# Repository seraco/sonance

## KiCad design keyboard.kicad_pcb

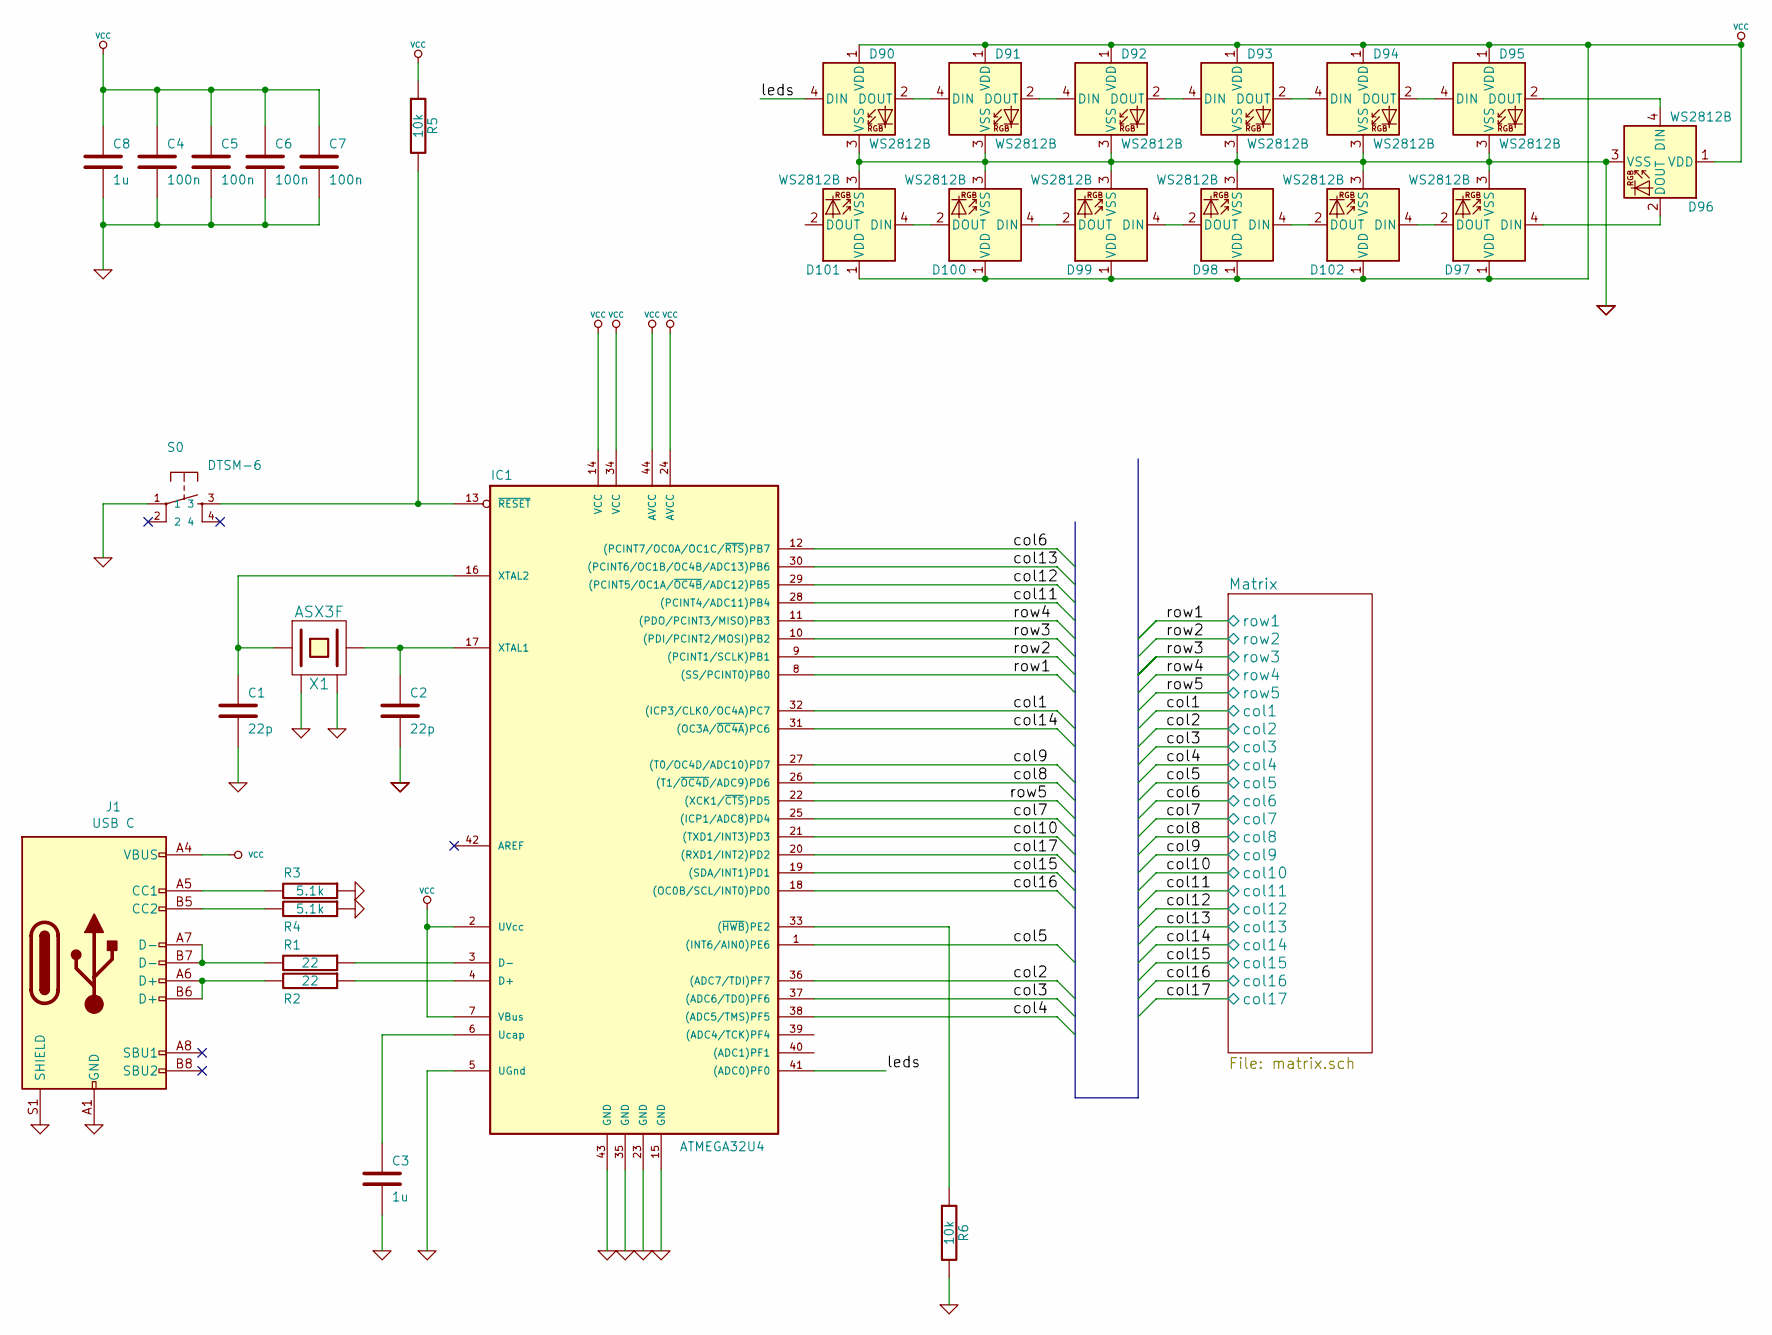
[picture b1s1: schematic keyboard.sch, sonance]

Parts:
C1, C2: 22p; 0805C; LCSC C1804
C3, C8: 1u; 0805C; LCSC C89190
C4, C5, C6, C7: 100n; 0805C; LCSC C1711
D90, D91, D92, D93, D94, D95, D96, D97, D98, D99, D100, D101, D102: WS2812B; LED_WS2812B_PLCC4_5.0x5.0mm_P3.2mm; LCSC C2761795
IC1: ATMEGA32U4; QFN-44-1EP_7x7mm_P0.5mm_EP5.2x5.2mm; LCSC C45874
J1: USB C; USB_C_Receptacle_Palconn_UTC16-G; LCSC C2835315
R1, R2: 22; 0805R; LCSC C17561
R3, R4: 5.1k; 0805R; LCSC C27834
R5, R6: 10k; 0805R; LCSC C17414
S0: DTSM-6; KSEM31GLFS; LCSC C221773
X1: ASX3F; 4-SMD; LCSC C258942

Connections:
/col1: IC1.32 ((ICP3/CLK0/OC4A)PC7); also elsewhere on the board
/col2: IC1.36 ((ADC7/TDI)PF7); also elsewhere on the board
/col3: IC1.37 ((ADC6/TDO)PF6); also elsewhere on the board
/col4: IC1.38 ((ADC5/TMS)PF5); also elsewhere on the board
/col5: IC1.1 ((INT6/AIN0)PE6); also elsewhere on the board
/col6: IC1.12 ((PCINT7/OC0A/OC1C/~RTS~)PB7); also elsewhere on the board
/col7: IC1.25 ((ICP1/ADC8)PD4); also elsewhere on the board
/col8: IC1.26 ((T1/~OC4D~/ADC9)PD6); also elsewhere on the board
/col9: IC1.27 ((T0/OC4D/ADC10)PD7); also elsewhere on the board
/col10: IC1.21 ((TXD1/INT3)PD3); also elsewhere on the board
/col11: IC1.28 ((PCINT4/ADC11)PB4); also elsewhere on the board
/col12: IC1.29 ((PCINT5/OC1A/~OC4B~/ADC12)PB5); also elsewhere on the board
/col13: IC1.30 ((PCINT6/OC1B/OC4B/ADC13)PB6); also elsewhere on the board
/col14: IC1.31 ((OC3A/~OC4A~)PC6); also elsewhere on the board
/col15: IC1.19 ((SDA/INT1)PD1); also elsewhere on the board
/col16: IC1.18 ((OC0B/SCL/INT0)PD0); also elsewhere on the board
/col17: IC1.20 ((RXD1/INT2)PD2); also elsewhere on the board
/leds: D90.4 (DIN), IC1.41 ((ADC0)PF0)
/row1: IC1.8 ((SS/PCINT0)PB0); also elsewhere on the board
/row2: IC1.9 ((PCINT1/SCLK)PB1); also elsewhere on the board
/row3: IC1.10 ((PDI/PCINT2/MOSI)PB2); also elsewhere on the board
/row4: IC1.11 ((PDO/PCINT3/MISO)PB3); also elsewhere on the board
/row5: IC1.22 ((XCK1/~CTS~)PD5); also elsewhere on the board
GND: C1.2, C2.2, C3.2, C4.2, C5.2, C6.2, C7.2, C8.2, D90.3 (VSS), D91.3 (VSS), D92.3 (VSS), D93.3 (VSS), D94.3 (VSS), D95.3 (VSS), D96.3 (VSS), D97.3 (VSS), D98.3 (VSS), D99.3 (VSS), D100.3 (VSS), D101.3 (VSS), D102.3 (VSS), IC1.5 (UGnd), IC1.15 (GND), IC1.23 (GND), IC1.35 (GND), IC1.43 (GND), J1.A1 (GND), J1.A12 (GND), J1.B1 (GND), J1.B12 (GND), J1.S1 (SHIELD), R3.1, R4.1, R6.2, S0.1, X1.2 (GND), X1.4 (GND)
unnamed: C1.1, IC1.16 (XTAL2), X1.1
unnamed: C2.1, IC1.17 (XTAL1), X1.3 (2)
unnamed: C3.1, IC1.6 (Ucap)
unnamed: D90.2 (DOUT), D91.4 (DIN)
unnamed: D91.2 (DOUT), D92.4 (DIN)
unnamed: D92.2 (DOUT), D93.4 (DIN)
unnamed: D93.2 (DOUT), D94.4 (DIN)
unnamed: D94.2 (DOUT), D95.4 (DIN)
unnamed: D95.2 (DOUT), D96.4 (DIN)
unnamed: D96.2 (DOUT), D97.4 (DIN)
unnamed: D98.2 (DOUT), D99.4 (DIN)
unnamed: D100.2 (DOUT), D101.4 (DIN)
unnamed: D99.2 (DOUT), D100.4 (DIN)
unnamed: D98.4 (DIN), D102.2 (DOUT)
unnamed: D97.2 (DOUT), D102.4 (DIN)
unnamed: IC1.3 (D-), R1.1
unnamed: IC1.4 (D+), R2.1
unnamed: IC1.13 (~RESET~), R5.2, S0.3
unnamed: IC1.33 ((~HWB~)PE2), R6.1
unnamed: J1.A5 (CC1), R3.2
unnamed: J1.A6 (D+), J1.B6 (D+), R2.2
unnamed: J1.A7 (D-), J1.B7 (D-), R1.2
unnamed: J1.B5 (CC2), R4.2
VCC: C4.1, C5.1, C6.1, C7.1, C8.1, D90.1 (VDD), D91.1 (VDD), D92.1 (VDD), D93.1 (VDD), D94.1 (VDD), D95.1 (VDD), D96.1 (VDD), D97.1 (VDD), D98.1 (VDD), D99.1 (VDD), D100.1 (VDD), D101.1 (VDD), D102.1 (VDD), IC1.2 (UVcc), IC1.7 (VBus), IC1.14 (VCC), IC1.24 (AVCC), IC1.34 (VCC), IC1.44 (AVCC), J1.A4 (VBUS), J1.A9 (VBUS), J1.B4 (VBUS), J1.B9 (VBUS), R5.1

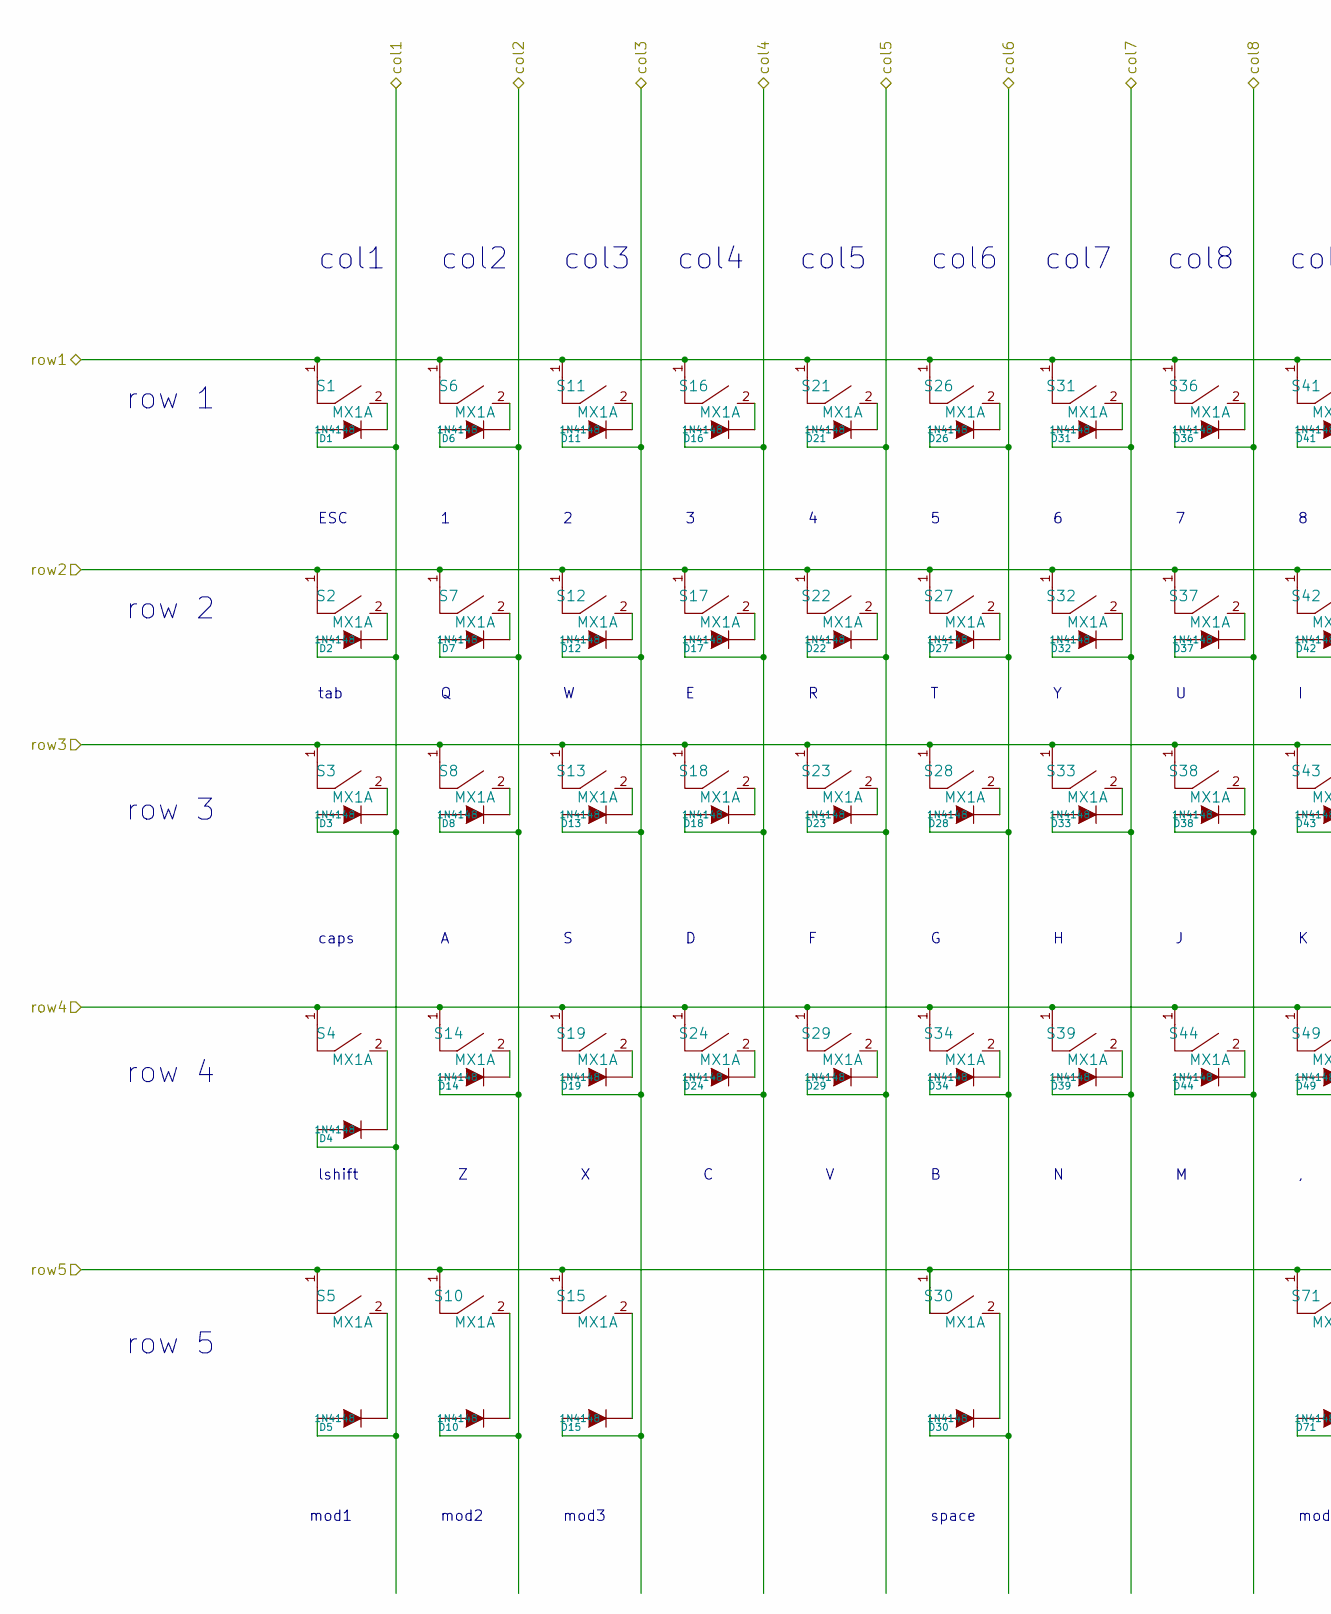
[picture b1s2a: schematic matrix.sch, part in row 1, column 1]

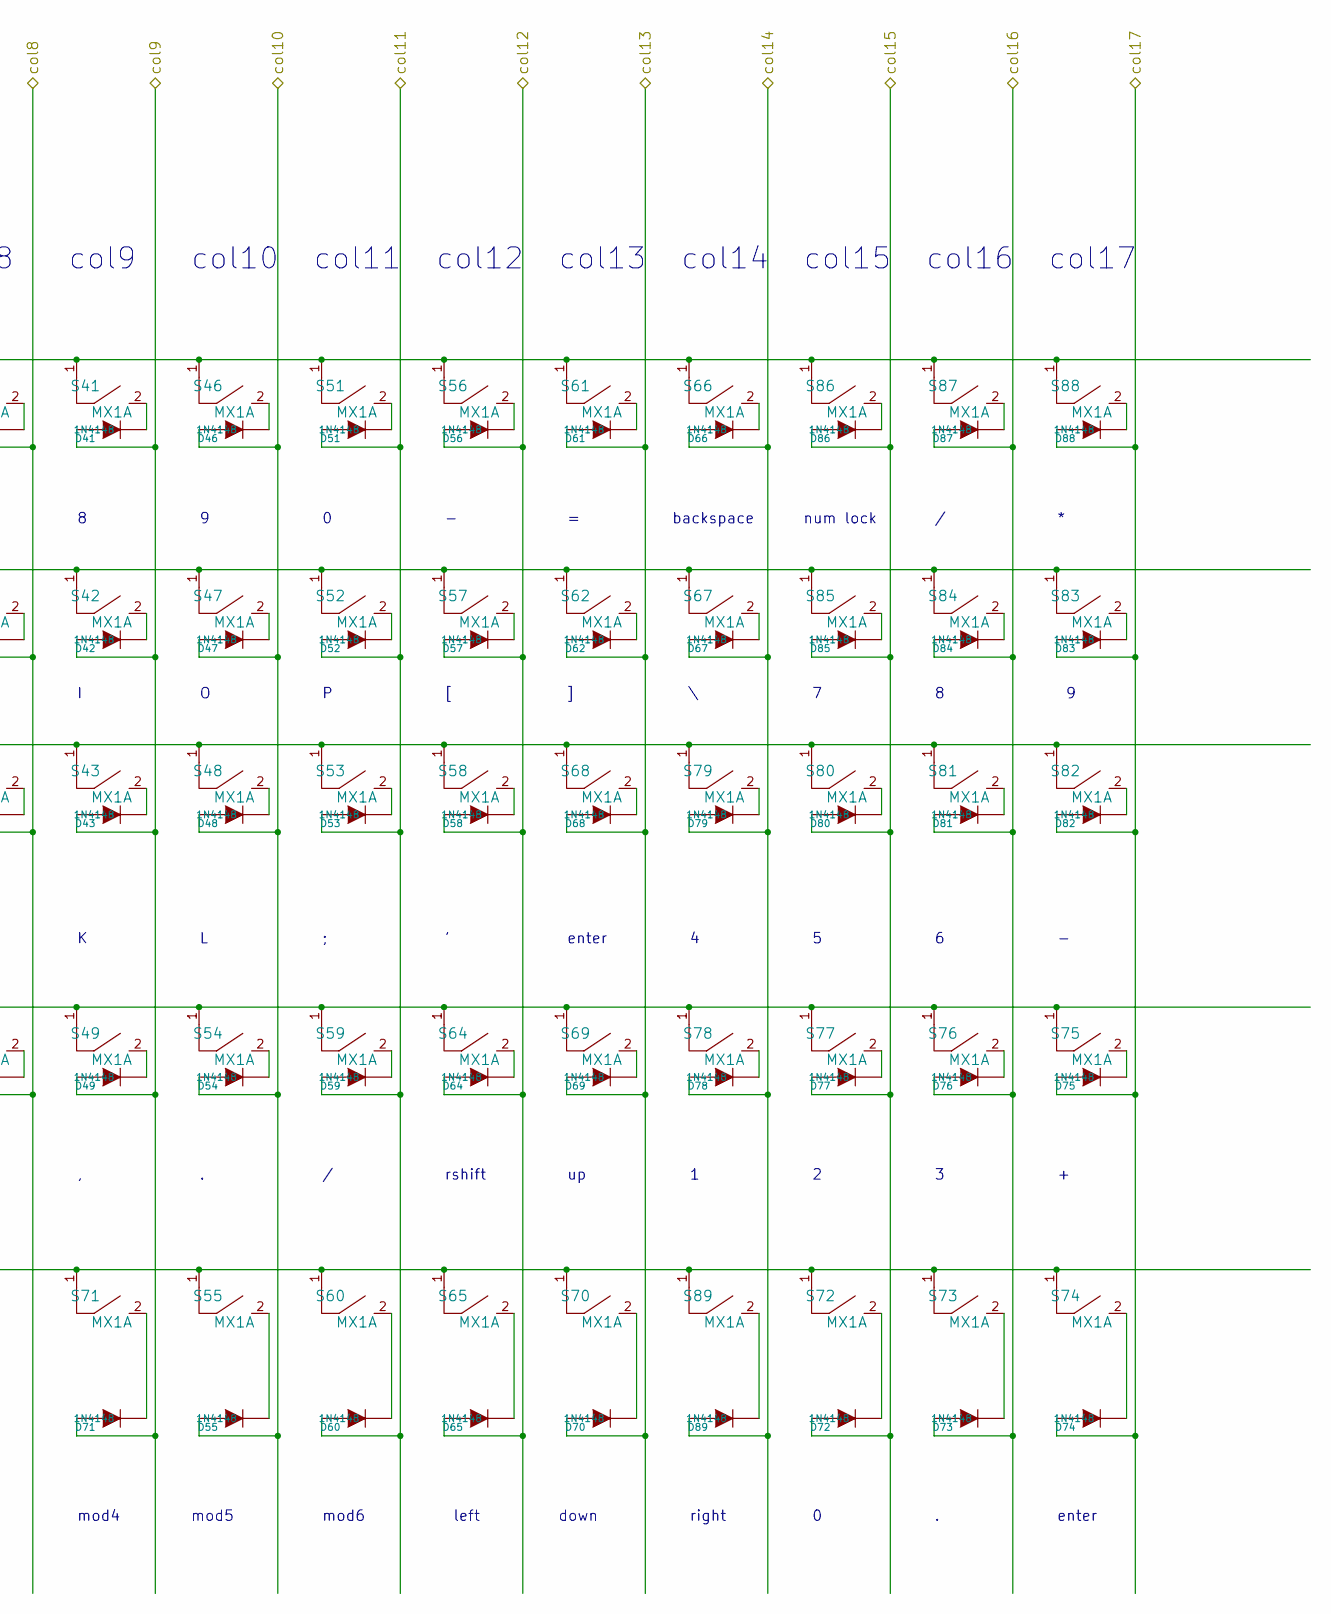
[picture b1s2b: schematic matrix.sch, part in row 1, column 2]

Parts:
D1, D2, D3, D4, D5, D6, D7, D8, D10, D11, D12, D13, D14, D15, D16, D17, D18, D19, D21, D22, D23, D24, D26, D27, D28, D29, D30, D31, D32, D33, D34, D36, D37, D38, D39, D41, D42, D43, D44, D46, D47, D48, D49, D51, D52, D53, D54, D55, D56, D57, D58, D59, D60, D61, D62, D64, D65, D66, D67, D68, D69, D70, D71, D72, D73, D74, D75, D76, D77, D78, D79, D80, D81, D82, D83, D84, D85, D86, D87, D88, D89: 1N4148; D_SOD-323F; LCSC C2128
S1, S2, S3, S4, S5, S6, S7, S8, S10, S11, S12, S13, S14, S15, S16, S17, S18, S19, S21, S22, S23, S24, S26, S27, S28, S29, S30, S31, S32, S33, S34, S36, S37, S38, S39, S41, S42, S43, S44, S46, S47, S48, S49, S51, S52, S53, S54, S55, S56, S57, S58, S59, S60, S61, S62, S64, S65, S66, S67, S68, S69, S70, S71, S72, S73, S74, S75, S76, S77, S78, S79, S80, S81, S82, S83, S84, S85, S86, S87, S88, S89: MX1A

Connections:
/col1: D1.1 (A), D2.1 (A), D3.1 (A), D4.1 (A), D5.1 (A); also elsewhere on the board
/col2: D6.1 (A), D7.1 (A), D8.1 (A), D10.1 (A), D14.1 (A); also elsewhere on the board
/col3: D11.1 (A), D12.1 (A), D13.1 (A), D15.1 (A), D19.1 (A); also elsewhere on the board
/col4: D16.1 (A), D17.1 (A), D18.1 (A), D24.1 (A); also elsewhere on the board
/col5: D21.1 (A), D22.1 (A), D23.1 (A), D29.1 (A); also elsewhere on the board
/col6: D26.1 (A), D27.1 (A), D28.1 (A), D30.1 (A), D34.1 (A); also elsewhere on the board
/col7: D31.1 (A), D32.1 (A), D33.1 (A), D39.1 (A); also elsewhere on the board
/col8: D36.1 (A), D37.1 (A), D38.1 (A), D44.1 (A); also elsewhere on the board
/col9: D41.1 (A), D42.1 (A), D43.1 (A), D49.1 (A), D71.1 (A); also elsewhere on the board
/col10: D46.1 (A), D47.1 (A), D48.1 (A), D54.1 (A), D55.1 (A); also elsewhere on the board
/col11: D51.1 (A), D52.1 (A), D53.1 (A), D59.1 (A), D60.1 (A); also elsewhere on the board
/col12: D56.1 (A), D57.1 (A), D58.1 (A), D64.1 (A), D65.1 (A); also elsewhere on the board
/col13: D61.1 (A), D62.1 (A), D68.1 (A), D69.1 (A), D70.1 (A); also elsewhere on the board
/col14: D66.1 (A), D67.1 (A), D78.1 (A), D79.1 (A), D89.1 (A); also elsewhere on the board
/col15: D72.1 (A), D77.1 (A), D80.1 (A), D85.1 (A), D86.1 (A); also elsewhere on the board
/col16: D73.1 (A), D76.1 (A), D81.1 (A), D84.1 (A), D87.1 (A); also elsewhere on the board
/col17: D74.1 (A), D75.1 (A), D82.1 (A), D83.1 (A), D88.1 (A); also elsewhere on the board
/row1: S1.1, S6.1, S11.1, S16.1, S21.1, S26.1, S31.1, S36.1, S41.1, S46.1, S51.1, S56.1, S61.1, S66.1, S86.1, S87.1, S88.1; also elsewhere on the board
/row2: S2.1, S7.1, S12.1, S17.1, S22.1, S27.1, S32.1, S37.1, S42.1, S47.1, S52.1, S57.1, S62.1, S67.1, S83.1, S84.1, S85.1; also elsewhere on the board
/row3: S3.1, S8.1, S13.1, S18.1, S23.1, S28.1, S33.1, S38.1, S43.1, S48.1, S53.1, S58.1, S68.1, S79.1, S80.1, S81.1, S82.1; also elsewhere on the board
/row4: S4.1, S14.1, S19.1, S24.1, S29.1, S34.1, S39.1, S44.1, S49.1, S54.1, S59.1, S64.1, S69.1, S75.1, S76.1, S77.1, S78.1; also elsewhere on the board
/row5: S5.1, S10.1, S15.1, S30.1, S55.1, S60.1, S65.1, S70.1, S71.1, S72.1, S73.1, S74.1, S89.1; also elsewhere on the board
unnamed: D1.2 (K), S1.2
unnamed: D2.2 (K), S2.2
unnamed: D3.2 (K), S3.2
unnamed: D4.2 (K), S4.2
unnamed: D5.2 (K), S5.2
unnamed: D6.2 (K), S6.2
unnamed: D7.2 (K), S7.2
unnamed: D8.2 (K), S8.2
unnamed: D10.2 (K), S10.2
unnamed: D11.2 (K), S11.2
unnamed: D12.2 (K), S12.2
unnamed: D13.2 (K), S13.2
unnamed: D14.2 (K), S14.2
unnamed: D15.2 (K), S15.2
unnamed: D16.2 (K), S16.2
unnamed: D17.2 (K), S17.2
unnamed: D18.2 (K), S18.2
unnamed: D19.2 (K), S19.2
unnamed: D21.2 (K), S21.2
unnamed: D22.2 (K), S22.2
unnamed: D23.2 (K), S23.2
unnamed: D24.2 (K), S24.2
unnamed: D26.2 (K), S26.2
unnamed: D27.2 (K), S27.2
unnamed: D28.2 (K), S28.2
unnamed: D29.2 (K), S29.2
unnamed: D30.2 (K), S30.2
unnamed: D31.2 (K), S31.2
unnamed: D32.2 (K), S32.2
unnamed: D33.2 (K), S33.2
unnamed: D34.2 (K), S34.2
unnamed: D36.2 (K), S36.2
unnamed: D37.2 (K), S37.2
unnamed: D38.2 (K), S38.2
unnamed: D39.2 (K), S39.2
unnamed: D41.2 (K), S41.2
unnamed: D42.2 (K), S42.2
unnamed: D43.2 (K), S43.2
unnamed: D44.2 (K), S44.2
unnamed: D46.2 (K), S46.2
unnamed: D47.2 (K), S47.2
unnamed: D48.2 (K), S48.2
unnamed: D49.2 (K), S49.2
unnamed: D51.2 (K), S51.2
unnamed: D52.2 (K), S52.2
unnamed: D53.2 (K), S53.2
unnamed: D54.2 (K), S54.2
unnamed: D55.2 (K), S55.2
unnamed: D56.2 (K), S56.2
unnamed: D57.2 (K), S57.2
unnamed: D58.2 (K), S58.2
unnamed: D59.2 (K), S59.2
unnamed: D60.2 (K), S60.2
unnamed: D61.2 (K), S61.2
unnamed: D62.2 (K), S62.2
unnamed: D64.2 (K), S64.2
unnamed: D65.2 (K), S65.2
unnamed: D66.2 (K), S66.2
unnamed: D67.2 (K), S67.2
unnamed: D68.2 (K), S68.2
unnamed: D69.2 (K), S69.2
unnamed: D70.2 (K), S70.2
unnamed: D71.2 (K), S71.2
unnamed: D72.2 (K), S72.2
unnamed: D73.2 (K), S73.2
unnamed: D74.2 (K), S74.2
unnamed: D75.2 (K), S75.2
unnamed: D76.2 (K), S76.2
unnamed: D77.2 (K), S77.2
unnamed: D78.2 (K), S78.2
unnamed: D79.2 (K), S79.2
unnamed: D80.2 (K), S80.2
unnamed: D81.2 (K), S81.2
unnamed: D82.2 (K), S82.2
unnamed: D83.2 (K), S83.2
unnamed: D84.2 (K), S84.2
unnamed: D85.2 (K), S85.2
unnamed: D86.2 (K), S86.2
unnamed: D87.2 (K), S87.2
unnamed: D88.2 (K), S88.2
unnamed: D89.2 (K), S89.2

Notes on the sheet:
row 1
row 2
row 3
row 4
row 5
col1
col2
col3
col4
col5
col6
col7
col9
col10
col11
col12
col13
col14
col8
ESC
backspace
tab
caps
enter
rshift
mod1
mod2
mod3
mod5
mod6
left
down
lshift
space
mod4
col15
col16
col17
right
num lock

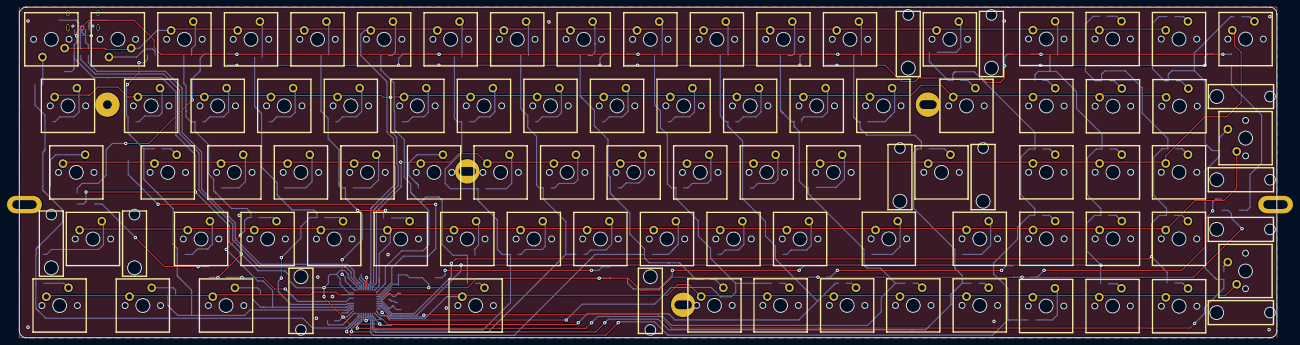
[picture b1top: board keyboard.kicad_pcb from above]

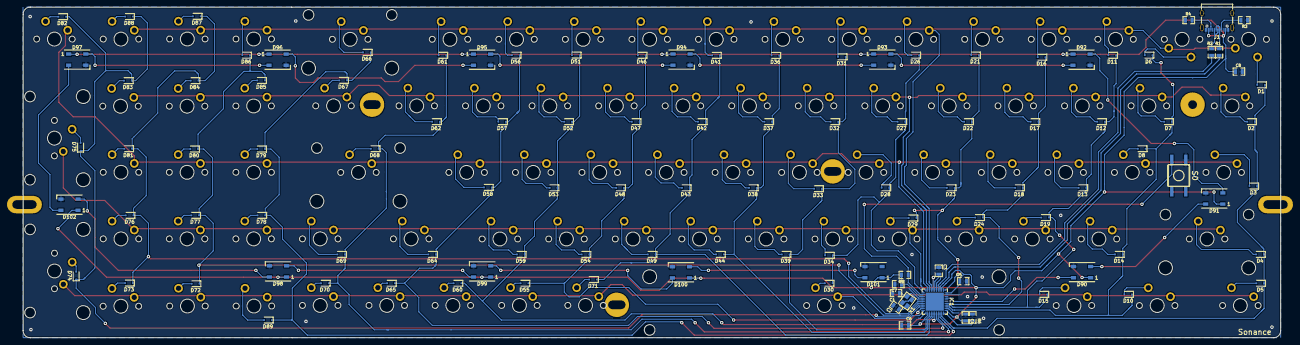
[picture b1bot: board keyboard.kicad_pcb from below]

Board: 2 copper layers, 359.9 x 94.6 mm, 211 parts (112 on the bottom side), 129 nets.

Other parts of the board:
HOLE: VAL**; PKRH
HOLE#2, HOLE#5: VAL**; PKRH
HOLE#3, HOLE#4: VAL**; PKRHSL
HOLE#6: VAL**; PKRHC
MXST: VAL**; MXST
MXST#2, MXST#3, MXST#4, MXST#5, MXST#6, MXST#7, MXST#8, MXST#9, MXST#10, MXST#11, MXST#12: VAL**; MXST

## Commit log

2022-01-03 Remove SW50 from PCB
2022-01-03 Remap project symbols
2022-01-03 Add keyboard layout for KLE
2022-01-03 Push keyboard-cache.lib and sym-lib-table
2022-01-03 Remove SW50 from matrix and leds
2022-01-03 Remove SW661
2022-01-04 Remove SW09 and SW041
2022-01-04 Add DB66 footprint back again
2022-01-04 Remove SW0512
2022-01-04 Remove unnecessary related SWs to S10
2022-01-04 Remove unnecessary related SW to SW15
2022-01-04 Remove unnecessary caps SW and related leds
2022-01-09 Remove unnecessary related SWs to SW30
2022-01-09 Remove unnecessary stabilizers for spacebar
2022-01-09 Remove unnecessary SWs next to enter
2022-01-09 Remove old layout around rswitch
2022-01-12 Remove leds from PCB
2022-01-12 Associate missing footprints
2022-01-13 Add rswitch and up buttons
2022-01-13 New PCB layout for bottom, left, mod4, mod5 and mod6
2022-01-13 Add drawing for numpad
2022-01-13 Change project details in PCB
2022-01-13 Extend edge cuts to accommodate numpad
2022-01-14 Remove GPIOs
2022-01-15 Start remapping of rows and cols in MCU
2022-01-15 Connected all rows in PCB
2022-01-15 Connect cols 1 to 3
2022-01-15 Connect col4
2022-01-15 Connect col5
2022-01-15 Connect col6
2022-01-15 Connect cols 7 to 9
2022-01-15 Connected cols 10 to 14
2022-01-15 Add numpad cols to schematic
2022-01-15 Prepare tracks for cols 15 to 18
2022-01-15 Extend GND zone to numpad
2022-01-15 Move right mounting hole to numpad
2022-01-15 Modify project info in matrix and schematic
2022-01-16 Rotate \ key
2022-01-16 Optimise matrix to save an additional pin on the MCU
2022-01-16 PCB with 3 pins ready for backlight
2022-01-16 Add all keys in PCB for numpad
2022-01-16 Rotate stabilisers on numpad
2022-01-16 Finish numpad in PCB
2022-01-16 Change position of oscillator
2022-01-16 Improve placement of C4 and R3
2022-01-19 Update schematic with USB C receptacle
2022-01-19 Assign footprint to USB C
2022-01-19 Update PCB to use USB Type C
2022-01-20 Adapt F.Fab and B.Fab to numpad
2022-01-20 Add /gerber to .gitignore
2022-01-20 Remove unnecessary info from silk layers
2022-01-20 Remove unnecessary logos and text
2022-01-20 Fill zones
2022-01-20 Run design rules check
2022-01-20 Update footprint in matrix
2022-01-21 Add leds to schematic
2022-01-21 Add VCC to all leds
2022-01-22 Add top leds in PCB
2022-01-22 Add an additional led to PCB
2022-01-22 Finish connecting all leds
2022-01-23 Make first row linear
2022-01-23 Make second row linear
2022-01-23 Make third row linear
2022-01-23 Make fourth row linear
2022-01-23 Tidy up columns
2022-01-23 Add ground via
2022-01-23 Update BOM
2022-01-23 Update BOM in schematic and matrix
2022-01-26 Change footprint for MCU
2022-01-26 Connect a few tracks to new QFN-44 package
2022-01-27 Connect new MCU and reduce trace width
2022-01-27 Change diode footprint
2022-01-28 Connect diode pads
2022-01-28 Generate BOM
2022-01-28 Fix cable not connected
2022-01-28 Send to manufacture
